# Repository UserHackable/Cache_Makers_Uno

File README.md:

## The Cache Makers Uno project

I created this board in the hopes of using it to teach a group of kids in the [Cache Makers](cachemakers.org) 4H program. 

The build met with mixed success. The board has a large number of solder points to solder in. The older students with a little more hand eye coordination and practice with soldering did ok, the Younger students struggled quite a bit more. 
The board, when completed does provide a functional Arduino Uno compatible device, with some extras for convenience when playing around beginning arduino programming. 

For the next session, I used the [YourDuino RoboRED](http://yourduino.com/sunshop2/index.php?l=product_detail&p=429) which I am a fan of. 
## CacheMakerUno 

### Board dimensions

* (220000, 220068) original units
* (2.2000, 2.2007) inches
* (55.8800, 55.8973) mm

| Front | Back |
| --- | --- |
|  |  |

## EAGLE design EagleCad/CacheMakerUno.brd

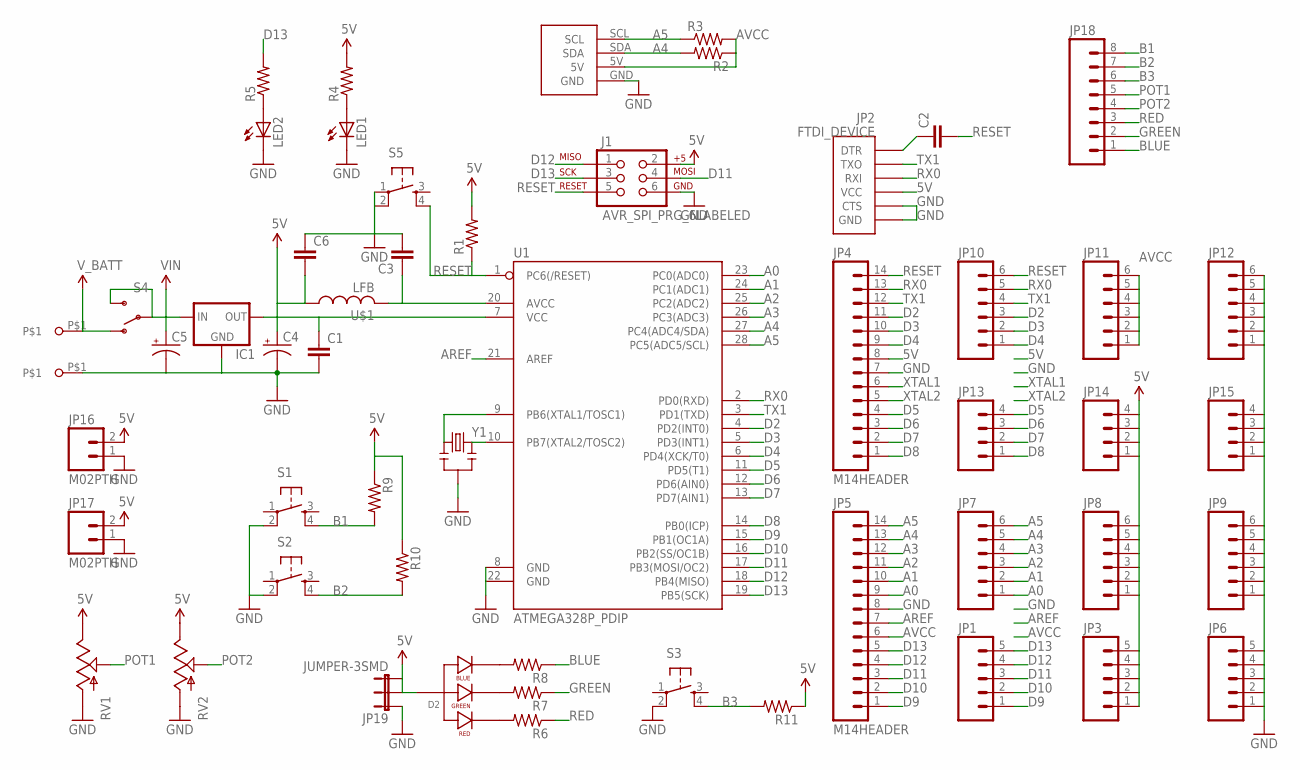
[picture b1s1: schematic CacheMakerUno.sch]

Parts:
C1, C2, C3, C6: CAPPTH; CAP-PTH-SMALL
C4, C5: CAP_POL2MM; CAP-PTH-2MM
D2: LED-RGB-CA-THRUDIFFUSE; LED-RGB-THRU
GND: M1; M1_NO_STRAIN
IC1: V_REG_78XXBASIC; TO-220-REG-BASIC
J1: AVR_SPI_PRG_6LABELED; 2X3-NS
JP1, JP3, JP6: M05NO_SILK; 1X05_NO_SILK
JP2: FTDI_DEVICE; FTDI_DEVICE_SIDE
JP4, JP5: M14HEADER; 1X14-HEADER
JP7, JP8, JP9, JP10, JP11, JP12: M06SIP; 1X06
JP13, JP14, JP15: M04PTH; 1X04
JP16, JP17: M02PTH; 1X02
JP18: M081X08; 1X08
JP19: JUMPER-3SMD; SJ_3
LED1, LED2: LED5MM
R1, R2, R3, R5: RESISTORAXIAL-0.3; AXIAL-0.3
R4, R6, R7, R8, R9, R10, R11: RESISTORPTH-1/4W-VERT; AXIAL-0.1
RV1, RV2: POTTRIM; TRIM_POT
S1, S2, S3, S5: TAC_SWITCHPTH; TACTILE-PTH
S4: SWITCH-SPDTPTH; SWITCH-SPDT
U1: ATMEGA328P_PDIP; DIL28-3
U$1: LFB; ALFB-01
U$2: I2C
V+: M1; M1_NO_STRAIN
Y1: RESONATORPTH; RESONATOR-PTH

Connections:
5V: C1.1, C4.+, C6.2, D2.2 (ANODE), IC1.3 (OUT), J1.2, JP2.P$4 (VCC), JP3.1, JP3.2, JP3.3, JP3.4, JP3.5, JP4.8, JP8.1, JP8.2, JP8.3, JP8.4, JP8.5, JP8.6, JP14.1, JP14.2, JP14.3, JP14.4, JP16.2, JP17.2, JP19.2, JP19.3, R1.P$2 (2), R4.P$2 (2), R9.P$1 (1), R10.P$1 (1), R11.P$1 (1), RV1.2 (E), RV2.2 (E), U1.7 (VCC), U$1.1
A0: JP5.9, JP7.1, U1.23 (PC0(ADC0))
A1: JP5.10, JP7.2, U1.24 (PC1(ADC1))
A2: JP5.11, JP7.3, U1.25 (PC2(ADC2))
A3: JP5.12, JP7.4, U1.26 (PC3(ADC3))
A4: JP5.13, JP7.5, R2.P$2 (2), U1.27 (PC4(ADC4/SDA)), U$2.SDA
A5: JP5.14, JP7.6, R3.P$1 (1), U1.28 (PC5(ADC5/SCL)), U$2.SCL
AREF: JP5.7, U1.21 (AREF)
AVCC: C3.1, JP5.6, JP11.1, JP11.2, JP11.3, JP11.4, JP11.5, JP11.6, R2.P$1 (1), R3.P$2 (2), U1.20 (AVCC), U$1.2, U$2.5V
B1: JP18.8, R9.P$2 (2), S1.4
B2: JP18.7, R10.P$2 (2), S2.4
B3: JP18.6, R11.P$2 (2), S3.4
BLUE: JP18.1, R8.P$1 (1)
D2: JP4.11, JP10.3, U1.4 (PD2(INT0))
D3: JP4.10, JP10.2, U1.5 (PD3(INT1))
D4: JP4.9, JP10.1, U1.6 (PD4(XCK/T0))
D5: JP4.4, JP13.4, U1.11 (PD5(T1))
D6: JP4.3, JP13.3, U1.12 (PD6(AIN0))
D7: JP4.2, JP13.2, U1.13 (PD7(AIN1))
D8: JP4.1, JP13.1, U1.14 (PB0(ICP))
D9: JP1.1, JP5.1, U1.15 (PB1(OC1A))
D10: JP1.2, JP5.2, U1.16 (PB2(SS/OC1B))
D11: J1.4, JP1.3, JP5.3, U1.17 (PB3(MOSI/OC2))
D12: J1.1, JP1.4, JP5.4, U1.18 (PB4(MISO))
D13: J1.3, JP1.5, JP5.5, R5.P$2 (2), U1.19 (PB5(SCK))
DTR: C2.1, JP2.P$1 (DTR)
GND: C1.2, C3.2, C4.-, C5.-, C6.1, GND.P$1, IC1.2 (GND), J1.6, JP2.P$5 (CTS), JP2.P$6 (GND), JP4.7, JP5.8, JP6.1, JP6.2, JP6.3, JP6.4, JP6.5, JP9.1, JP9.2, JP9.3, JP9.4, JP9.5, JP9.6, JP12.1, JP12.2, JP12.3, JP12.4, JP12.5, JP12.6, JP15.1, JP15.2, JP15.3, JP15.4, JP16.1, JP17.1, JP19.1, LED1.K (C), LED2.K (C), RV1.3 (A), RV2.3 (A), S1.2, S2.2, S3.2, S5.1, S5.2, U1.8 (GND), U1.22 (GND), U$2.GND, Y1.2
GREEN: JP18.2, R7.P$1 (1)
unnamed: LED1.A, R4.P$1 (1)
unnamed: LED2.A, R5.P$1 (1)
unnamed: D2.1 (RED_CATHODE), R6.P$2 (2)
unnamed: D2.3 (GREEN_CATHODE), R7.P$2 (2)
unnamed: D2.4 (BLUE_CATHODE), R8.P$2 (2)
POT1: JP18.5, RV1.1 (S)
POT2: JP18.4, RV2.1 (S)
RED: JP18.3, R6.P$1 (1)
RESET: C2.2, J1.5, JP4.14, JP10.6, R1.P$1 (1), S5.4, U1.1 (PC6(/RESET))
RX0: JP2.P$3 (RXI), JP4.13, JP10.5, U1.2 (PD0(RXD))
TX1: JP2.P$2 (TXO), JP4.12, JP10.4, U1.3 (PD1(TXD))
VIN: C5.+, IC1.1 (IN), S4.2, S4.3 (S)
V_BATT: S4.1 (O), V+.P$1
XTAL1: JP4.6, U1.9 (PB6(XTAL1/TOSC1)), Y1.1
XTAL2: JP4.5, U1.10 (PB7(XTAL2/TOSC2)), Y1.3

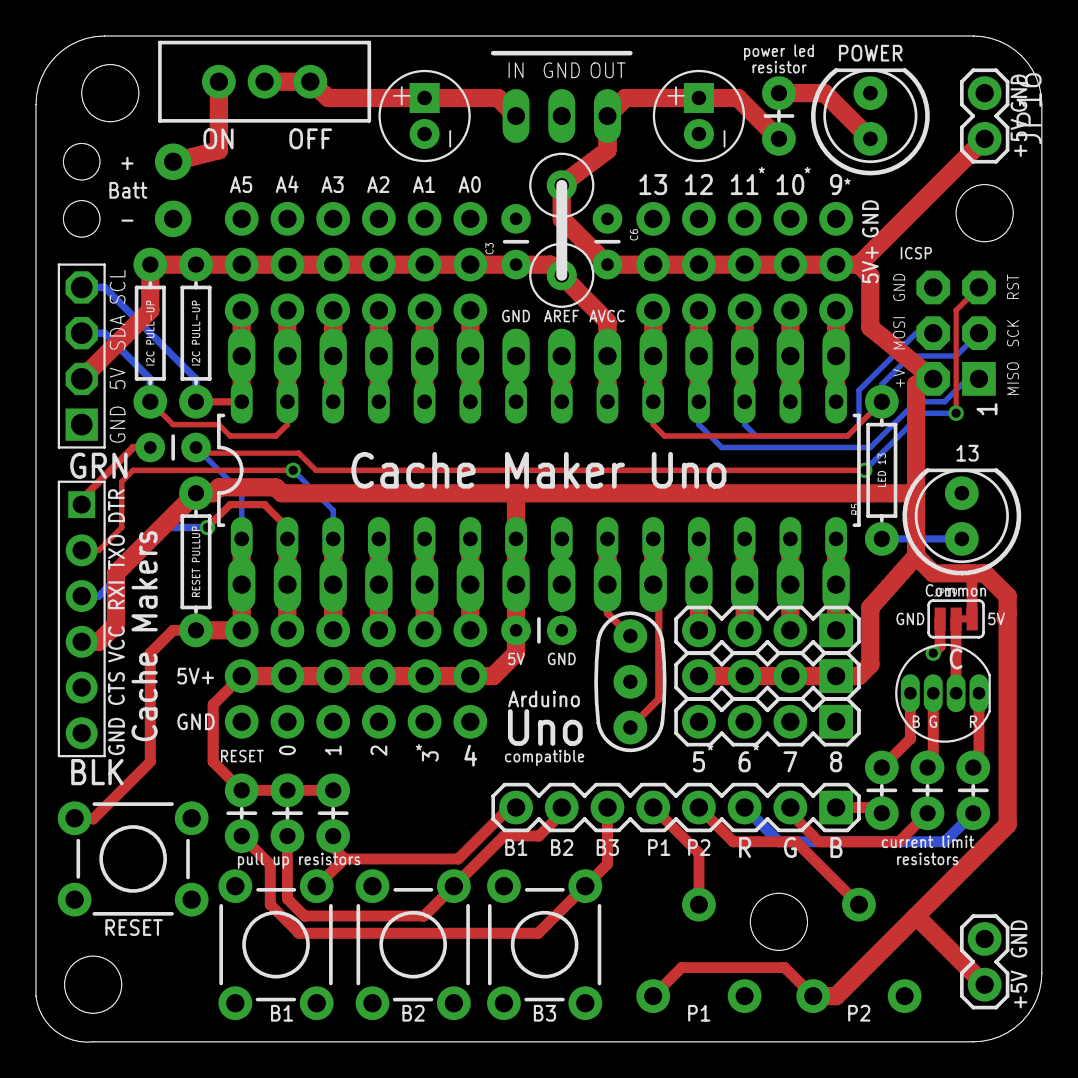
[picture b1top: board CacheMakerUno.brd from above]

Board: 2 copper layers, 55.9 x 55.9 mm, 54 parts (0 on the bottom side), 43 nets.

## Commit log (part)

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2016-04-08 from Makefile

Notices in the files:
parts and their libraries:
SparkFun-Connectors: Licensing: Creative Commons ShareAlike 4.0 International - https://creativecommons.org/licenses/by-sa/4.0
